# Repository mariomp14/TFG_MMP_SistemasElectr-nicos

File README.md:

# TFG_MMP_SistemasElectrónicos
Este repositorio fue creado como complemento de mi TFG para compartir:

### 1. **Firmware/**
Contiene el código fuente desarrollado:
- Programas escritos en C/C++.  
- Configuraciones y bibliotecas necesarias (CMake, scripts, etc.).

### 2. **PCBs/**
Incluye todos los archivos relacionados con el diseño y fabricación de la placa:
- `esquemas/`: diagramas eléctricos en formato `.sch` (KiCad).
- `diseño/`: los diseños en `.kicad_pcb`, `.pro`, `.kicad_sch`.
- `gerbers/`: los archivos estándares para fabricación.
- `pick_and_place/`: archivos `.csv` o `.pos` con coordenadas de colocación de componentes.

---

##  ¿Cómo usar este repositorio?

1. **Firmware**:
   - Clona el repositorio.
   - Ingresa al directorio `Firmware`.
   - Entiende el código y utilizalo en tu microcontrolador de Espressif!

2. **PCBs**:
   - Abre el diseño en KiCad.
   - Revisa esquemáticos y layout.
   - Si deseas fabricar, usa los Gerbers y el archivo de taladrado.

---

##  Contribuye

¿Quieres colaborar o revisar el proyecto?  
— Si deseas utilizar algún recurso, contrinuir mejoras o discutir ideas, **abre un issue** o envía un **Pull Request**. ¡Toda ayuda es bien recibida!

---

¡Gracias por explorar mi trabajo!  
— Mario (mariomp14)

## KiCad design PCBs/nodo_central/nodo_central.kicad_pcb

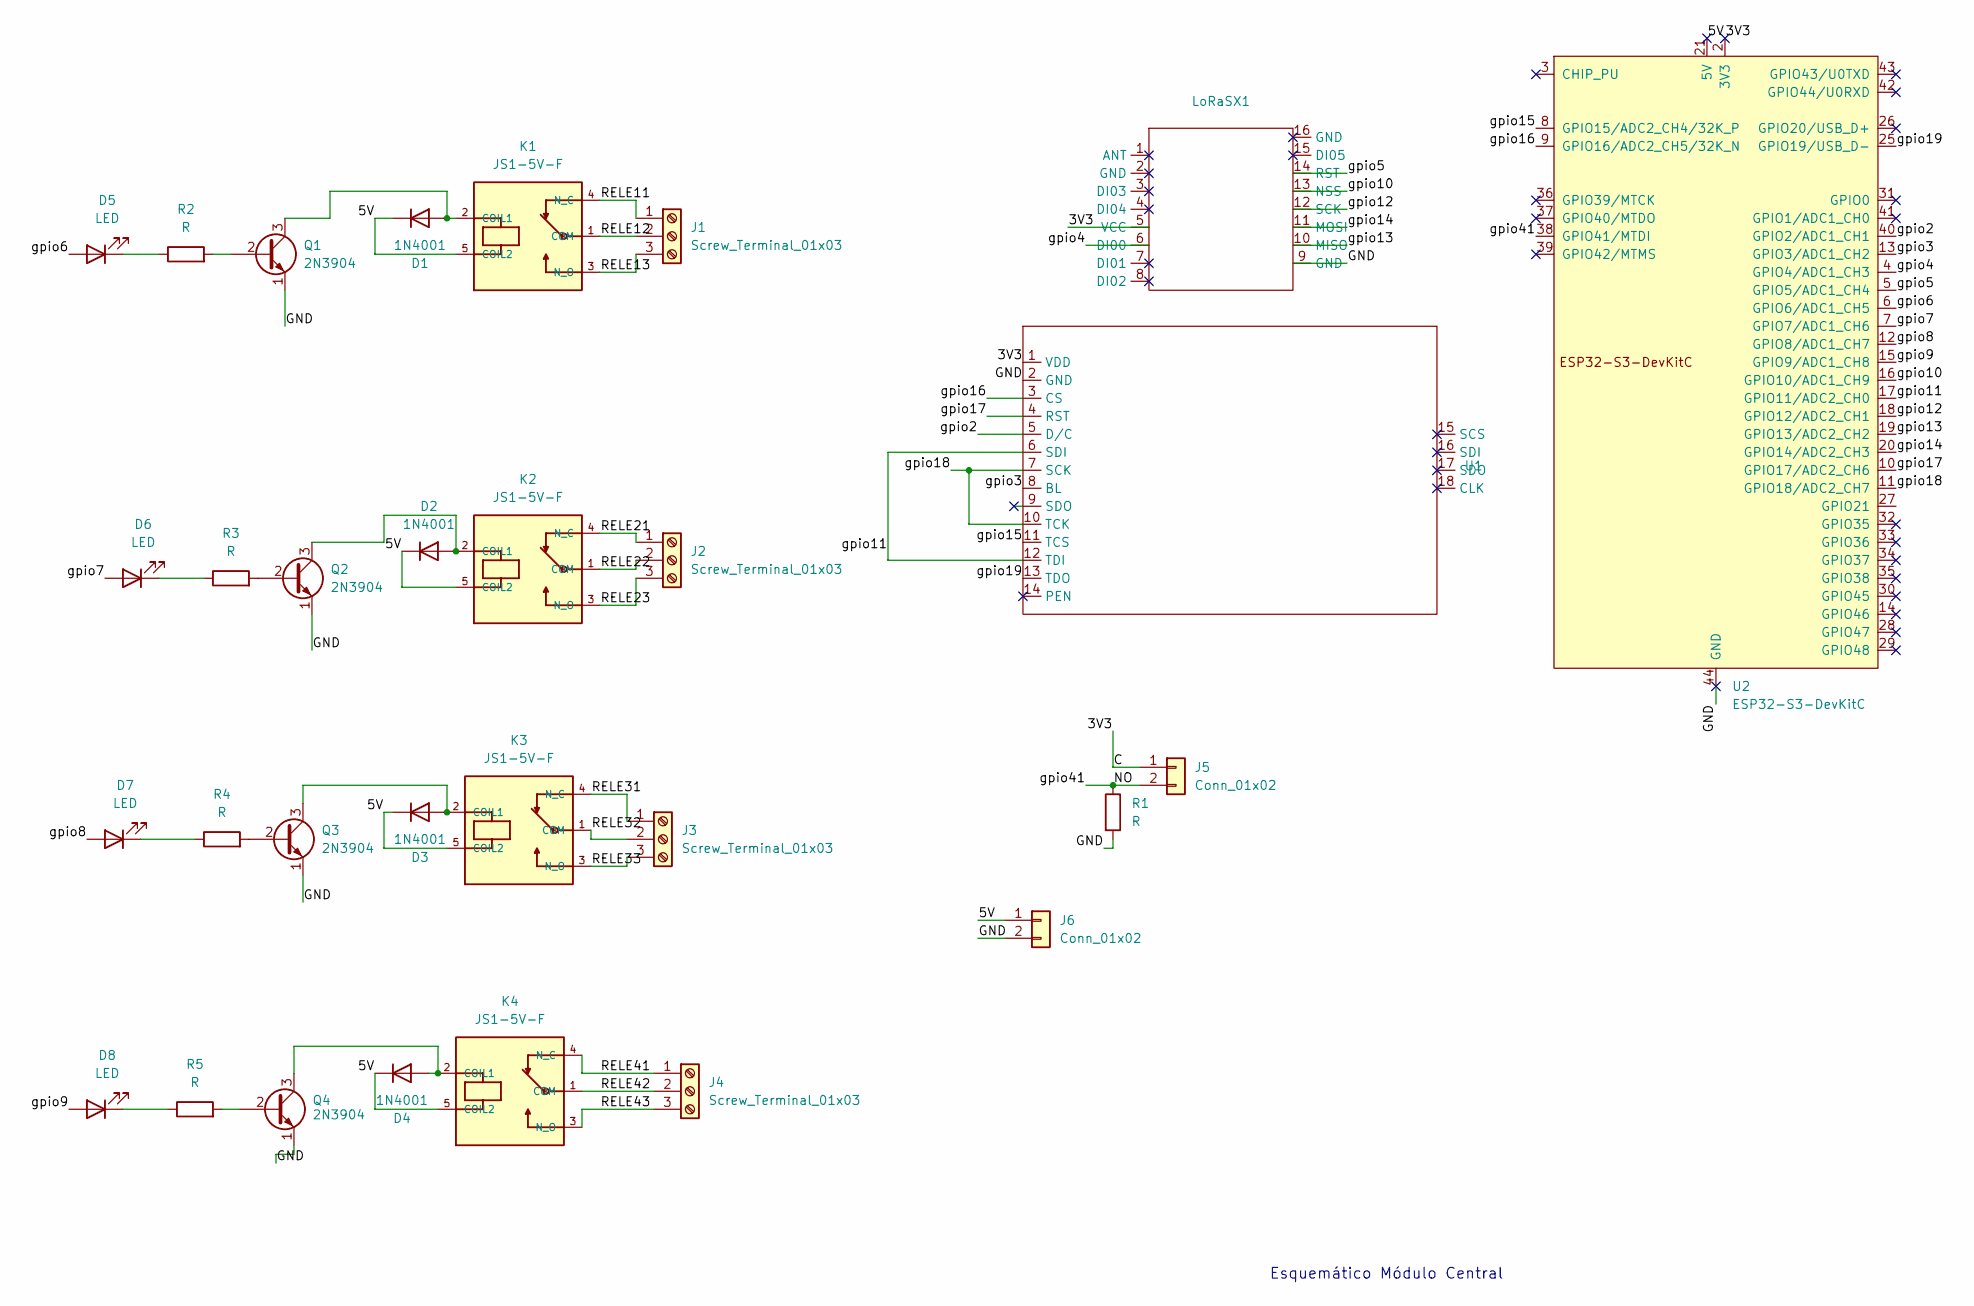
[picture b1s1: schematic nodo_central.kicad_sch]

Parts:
D1, D2, D3, D4: 1N4001; D_DO-41_SOD81_P10.16mm_Horizontal
D5, D6, D7, D8: LED; LED_D5.0mm
J1, J2, J3, J4: Screw_Terminal_01x03; TerminalBlock_bornier-3_P5.08mm
J5, J6: Conn_01x02; PinHeader_1x02_P2.54mm_Vertical
K1, K2, K3, K4: JS1-5V-F; RELAY_JS1-5V-F; PARTREV N/A
LoRaSX1: XCVR_RFM95W-868S2
Q1, Q2, Q3, Q4: 2N3904; TO-92_Inline_Wide
R1, R2, R3, R4, R5: R; R_Axial_DIN0207_L6.3mm_D2.5mm_P7.62mm_Horizontal
U1: ILI9488
U2: ESP32-S3-DevKitC

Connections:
/3V3: J5.1, LoRaSX1.5 (VCC), U1.1 (VDD), U2.1 (3V3), U2.2 (3V3)
/5V: D1.1 (K), D2.1 (K), D3.1 (K), D4.1 (K), J6.1, K1.5 (COIL2), K2.5 (COIL2), K3.5 (COIL2), K4.5 (COIL2), U2.21 (5V)
/GND: J6.2, LoRaSX1.9 (GND), Q1.1 (E), Q2.1 (E), Q3.1 (E), Q4.1 (E), R1.2, U1.2 (GND), U2.22 (GND), U2.23 (GND), U2.24 (GND), U2.44 (GND)
/NO: J5.2, R1.1, U2.38 (GPIO41/MTDI)
/RELE11: J1.1, K1.4 (N_C)
/RELE12: J1.2, K1.1 (COM)
/RELE13: J1.3, K1.3 (N_O)
/RELE21: J2.1, K2.4 (N_C)
/RELE22: J2.2, K2.1 (COM)
/RELE23: J2.3, K2.3 (N_O)
/RELE31: J3.1, K3.4 (N_C)
/RELE32: J3.2, K3.1 (COM)
/RELE33: J3.3, K3.3 (N_O)
/RELE41: J4.1, K4.4 (N_C)
/RELE42: J4.2, K4.1 (COM)
/RELE43: J4.3, K4.3 (N_O)
/gpio2: U1.5 (D/C), U2.40 (GPIO2/ADC1_CH1)
/gpio3: U1.8 (BL), U2.13 (GPIO3/ADC1_CH2)
/gpio4: LoRaSX1.6 (DI00), U2.4 (GPIO4/ADC1_CH3)
/gpio5: LoRaSX1.14 (RST), U2.5 (GPIO5/ADC1_CH4)
/gpio6: D5.2 (A), U2.6 (GPIO6/ADC1_CH5)
/gpio7: D6.2 (A), U2.7 (GPIO7/ADC1_CH6)
/gpio8: D7.2 (A), U2.12 (GPIO8/ADC1_CH7)
/gpio9: D8.2 (A), U2.15 (GPIO9/ADC1_CH8)
/gpio10: LoRaSX1.13 (NSS), U2.16 (GPIO10/ADC1_CH9)
/gpio11: U1.6 (SDI), U1.12 (TDI), U2.17 (GPIO11/ADC2_CH0)
/gpio12: LoRaSX1.12 (SCK), U2.18 (GPIO12/ADC2_CH1)
/gpio13: LoRaSX1.10 (MISO), U2.19 (GPIO13/ADC2_CH2)
/gpio14: LoRaSX1.11 (MOSI), U2.20 (GPIO14/ADC2_CH3)
/gpio15: U1.11 (TCS), U2.8 (GPIO15/ADC2_CH4/32K_P)
/gpio16: U1.3 (CS), U2.9 (GPIO16/ADC2_CH5/32K_N)
/gpio17: U1.4 (RST), U2.10 (GPIO17/ADC2_CH6)
/gpio18: U1.7 (SCK), U1.10 (TCK), U2.11 (GPIO18/ADC2_CH7)
/gpio19: U1.13 (TDO), U2.25 (GPIO19/USB_D-)
unnamed: D1.2 (A), K1.2 (COIL1), Q1.3 (C)
unnamed: D2.2 (A), K2.2 (COIL1), Q2.3 (C)
unnamed: D3.2 (A), K3.2 (COIL1), Q3.3 (C)
unnamed: D4.2 (A), K4.2 (COIL1), Q4.3 (C)
unnamed: D5.1 (K), R2.1
unnamed: D6.1 (K), R3.1
unnamed: D7.1 (K), R4.1
unnamed: D8.1 (K), R5.1
unnamed: Q1.2 (B), R2.2
unnamed: Q2.2 (B), R3.2
unnamed: Q3.2 (B), R4.2
unnamed: Q4.2 (B), R5.2

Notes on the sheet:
Esquemático Módulo Central

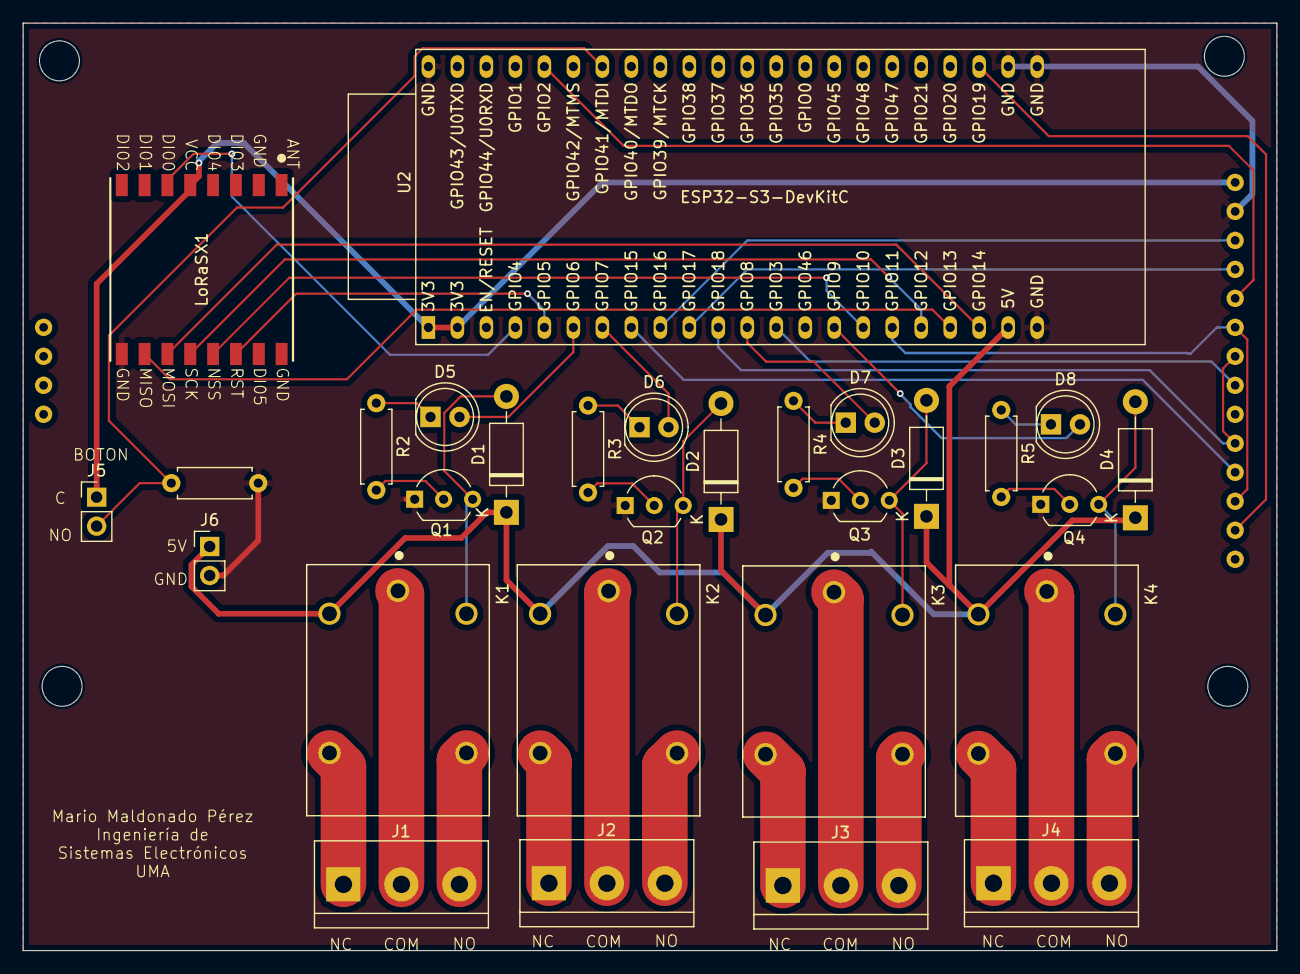
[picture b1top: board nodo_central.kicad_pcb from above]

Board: 2 copper layers, 109.8 x 81.3 mm, 30 parts (1 on the bottom side), 46 nets.

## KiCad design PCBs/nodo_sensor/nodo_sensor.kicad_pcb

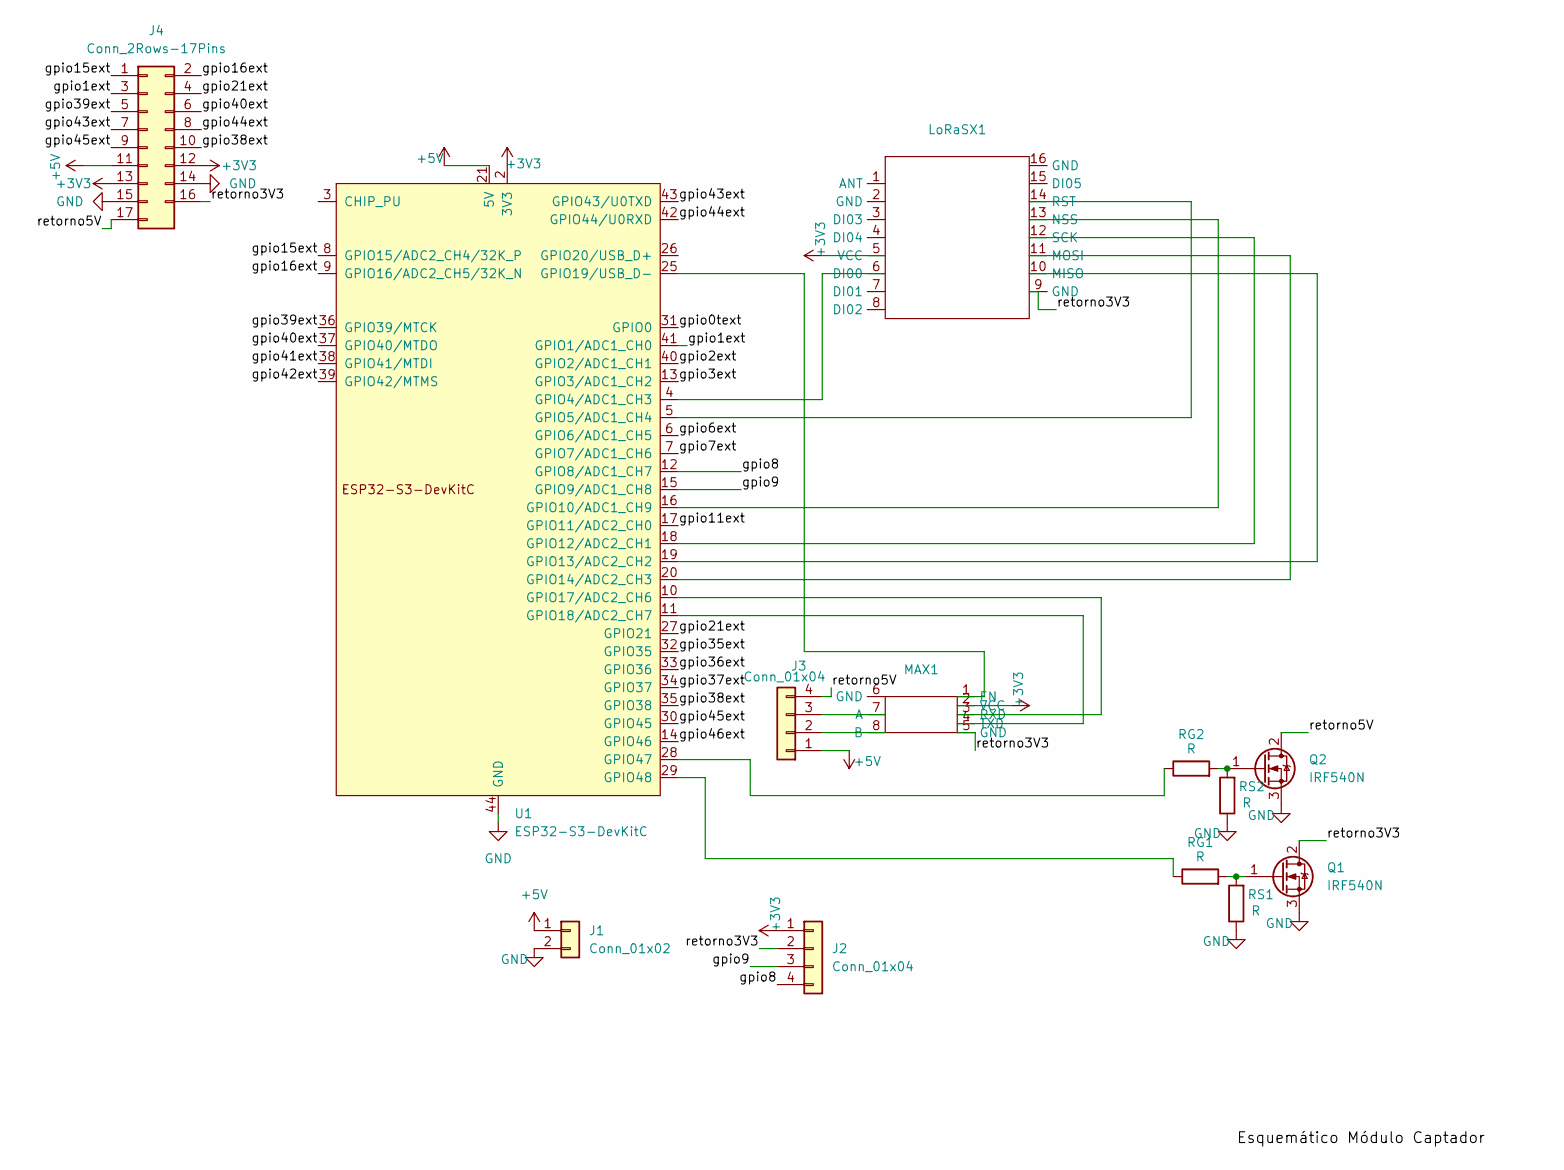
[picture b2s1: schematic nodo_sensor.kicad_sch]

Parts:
J1: Conn_01x02; PinHeader_1x02_P2.54mm_Vertical
J2: Conn_01x04; PinHeader_1x04_P2.54mm_Vertical_Humedad
J3: Conn_01x04; PinHeader_1x04_P2.54mm_Vertical_Suelo
J4: Conn_2Rows-17Pins; PinHeader_2x09_P2.54mm_Vertical
LoRaSX1: XCVR_RFM95W-868S2
MAX1: MAX3485
Q1, Q2: IRF540N; TO-220-3_Vertical
RG1, RG2: R; R_Axial_DIN0207_L6.3mm_D2.5mm_P7.62mm_Horizontal
RS1, RS2: R; R_Axial_DIN0207_L6.3mm_D2.5mm_P7.62mm_Horizontal
U1: ESP32-S3-DevKitC

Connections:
+3V3: J2.1, J4.12, J4.13, LoRaSX1.5 (VCC), MAX1.2 (VCC), U1.1 (3V3), U1.2 (3V3)
+5V: J1.1, J3.1, J4.11, U1.21 (5V)
/gpio0text: U1.31 (GPIO0)
/gpio1ext: J4.3, U1.41 (GPIO1/ADC1_CH0)
/gpio2ext: U1.40 (GPIO2/ADC1_CH1)
/gpio3ext: U1.13 (GPIO3/ADC1_CH2)
/gpio6ext: U1.6 (GPIO6/ADC1_CH5)
/gpio7ext: U1.7 (GPIO7/ADC1_CH6)
/gpio8: J2.4, U1.12 (GPIO8/ADC1_CH7)
/gpio9: J2.3, U1.15 (GPIO9/ADC1_CH8)
/gpio11ext: U1.17 (GPIO11/ADC2_CH0)
/gpio15ext: J4.1 (gpio15), U1.8 (GPIO15/ADC2_CH4/32K_P)
/gpio16ext: J4.2, U1.9 (GPIO16/ADC2_CH5/32K_N)
/gpio21ext: J4.4, U1.27 (GPIO21)
/gpio35ext: U1.32 (GPIO35)
/gpio36ext: U1.33 (GPIO36)
/gpio37ext: U1.34 (GPIO37)
/gpio38ext: J4.10, U1.35 (GPIO38)
/gpio39ext: J4.5, U1.36 (GPIO39/MTCK)
/gpio40ext: J4.6, U1.37 (GPIO40/MTDO)
/gpio41ext: U1.38 (GPIO41/MTDI)
/gpio42ext: U1.39 (GPIO42/MTMS)
/gpio43ext: J4.7, U1.43 (GPIO43/U0TXD)
/gpio44ext: J4.8, U1.42 (GPIO44/U0RXD)
/gpio45ext: J4.9, U1.30 (GPIO45)
/gpio46ext: U1.14 (GPIO46)
/retorno3V3: J2.2, J4.16, LoRaSX1.9 (GND), MAX1.5 (GND), Q1.2 (D)
/retorno5V: J3.4, J4.17, Q2.2 (D)
GND: J1.2, J4.14, J4.15, Q1.3 (S), Q2.3 (S), RS1.1, RS2.1, U1.22 (GND), U1.23 (GND), U1.24 (GND), U1.44 (GND)
unnamed: J3.2, MAX1.8 (B)
unnamed: J3.3, MAX1.7 (A)
unnamed: LoRaSX1.6 (DI00), U1.4 (GPIO4/ADC1_CH3)
unnamed: LoRaSX1.10 (MISO), U1.19 (GPIO13/ADC2_CH2)
unnamed: LoRaSX1.11 (MOSI), U1.20 (GPIO14/ADC2_CH3)
unnamed: LoRaSX1.13 (NSS), U1.16 (GPIO10/ADC1_CH9)
unnamed: LoRaSX1.14 (RST), U1.5 (GPIO5/ADC1_CH4)
unnamed: LoRaSX1.12 (SCK), U1.18 (GPIO12/ADC2_CH1)
unnamed: MAX1.1 (EN), U1.25 (GPIO19/USB_D-)
unnamed: MAX1.3 (RXD), U1.10 (GPIO17/ADC2_CH6)
unnamed: MAX1.4 (TXD), U1.11 (GPIO18/ADC2_CH7)
unnamed: Q1.1 (G), RG1.2, RS1.2
unnamed: Q2.1 (G), RG2.2, RS2.2
unnamed: RG2.1, U1.28 (GPIO47)
unnamed: RG1.1, U1.29 (GPIO48)

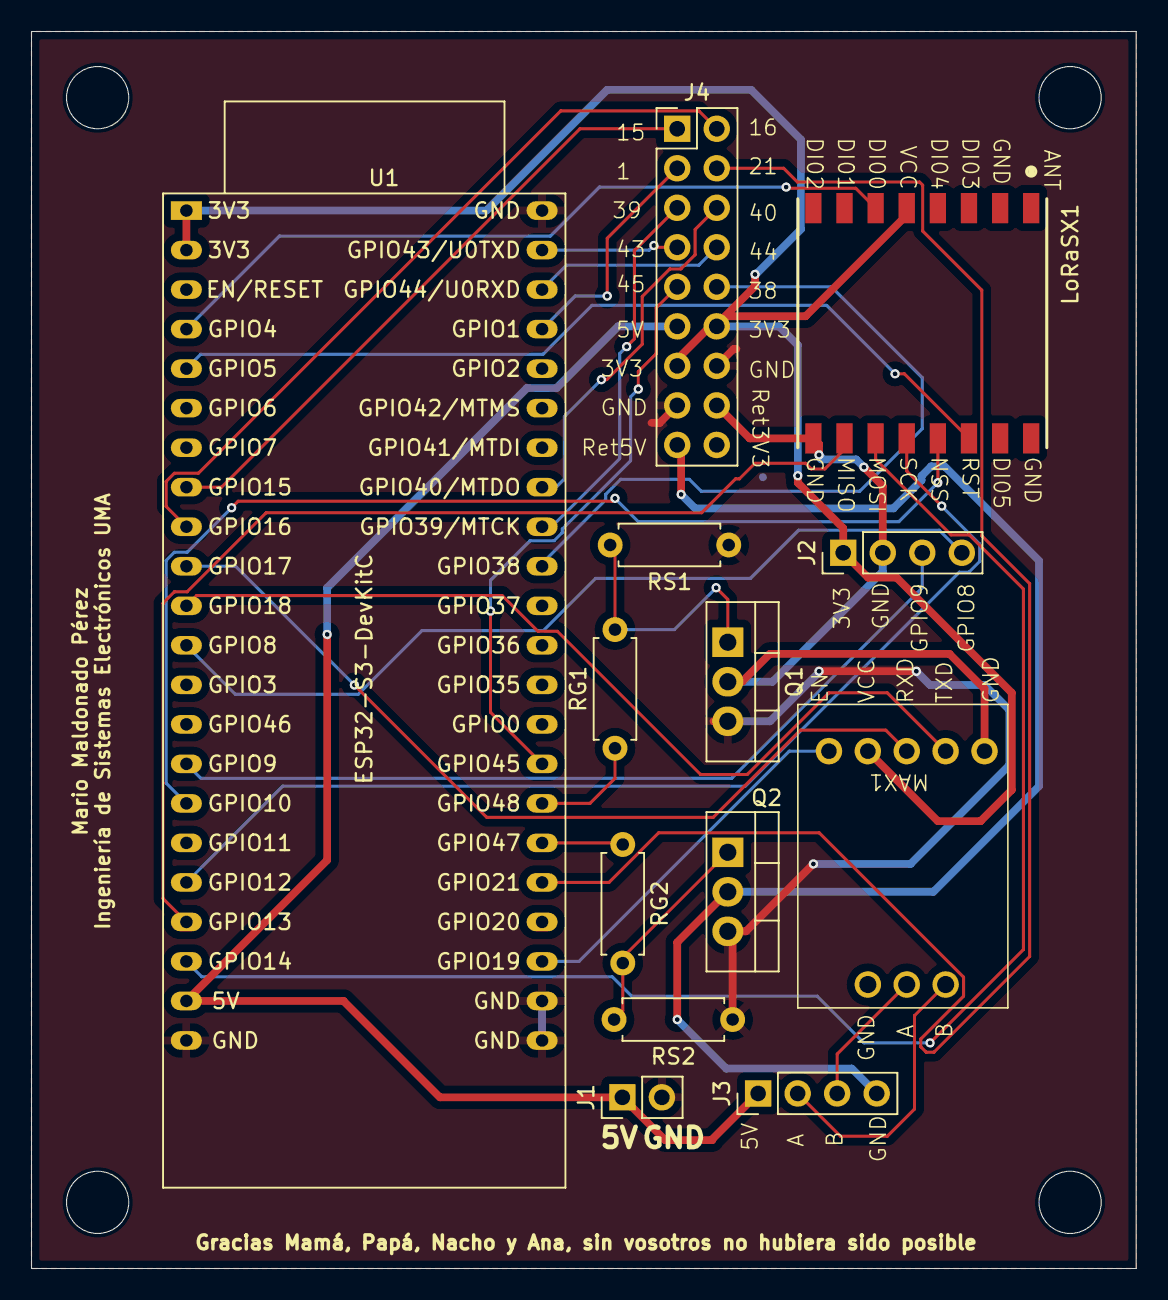
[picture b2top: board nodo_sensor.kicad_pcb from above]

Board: 2 copper layers, 71.0 x 79.5 mm, 13 parts (0 on the bottom side), 32 nets.

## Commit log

2025-08-25 Repositorio_TFG
